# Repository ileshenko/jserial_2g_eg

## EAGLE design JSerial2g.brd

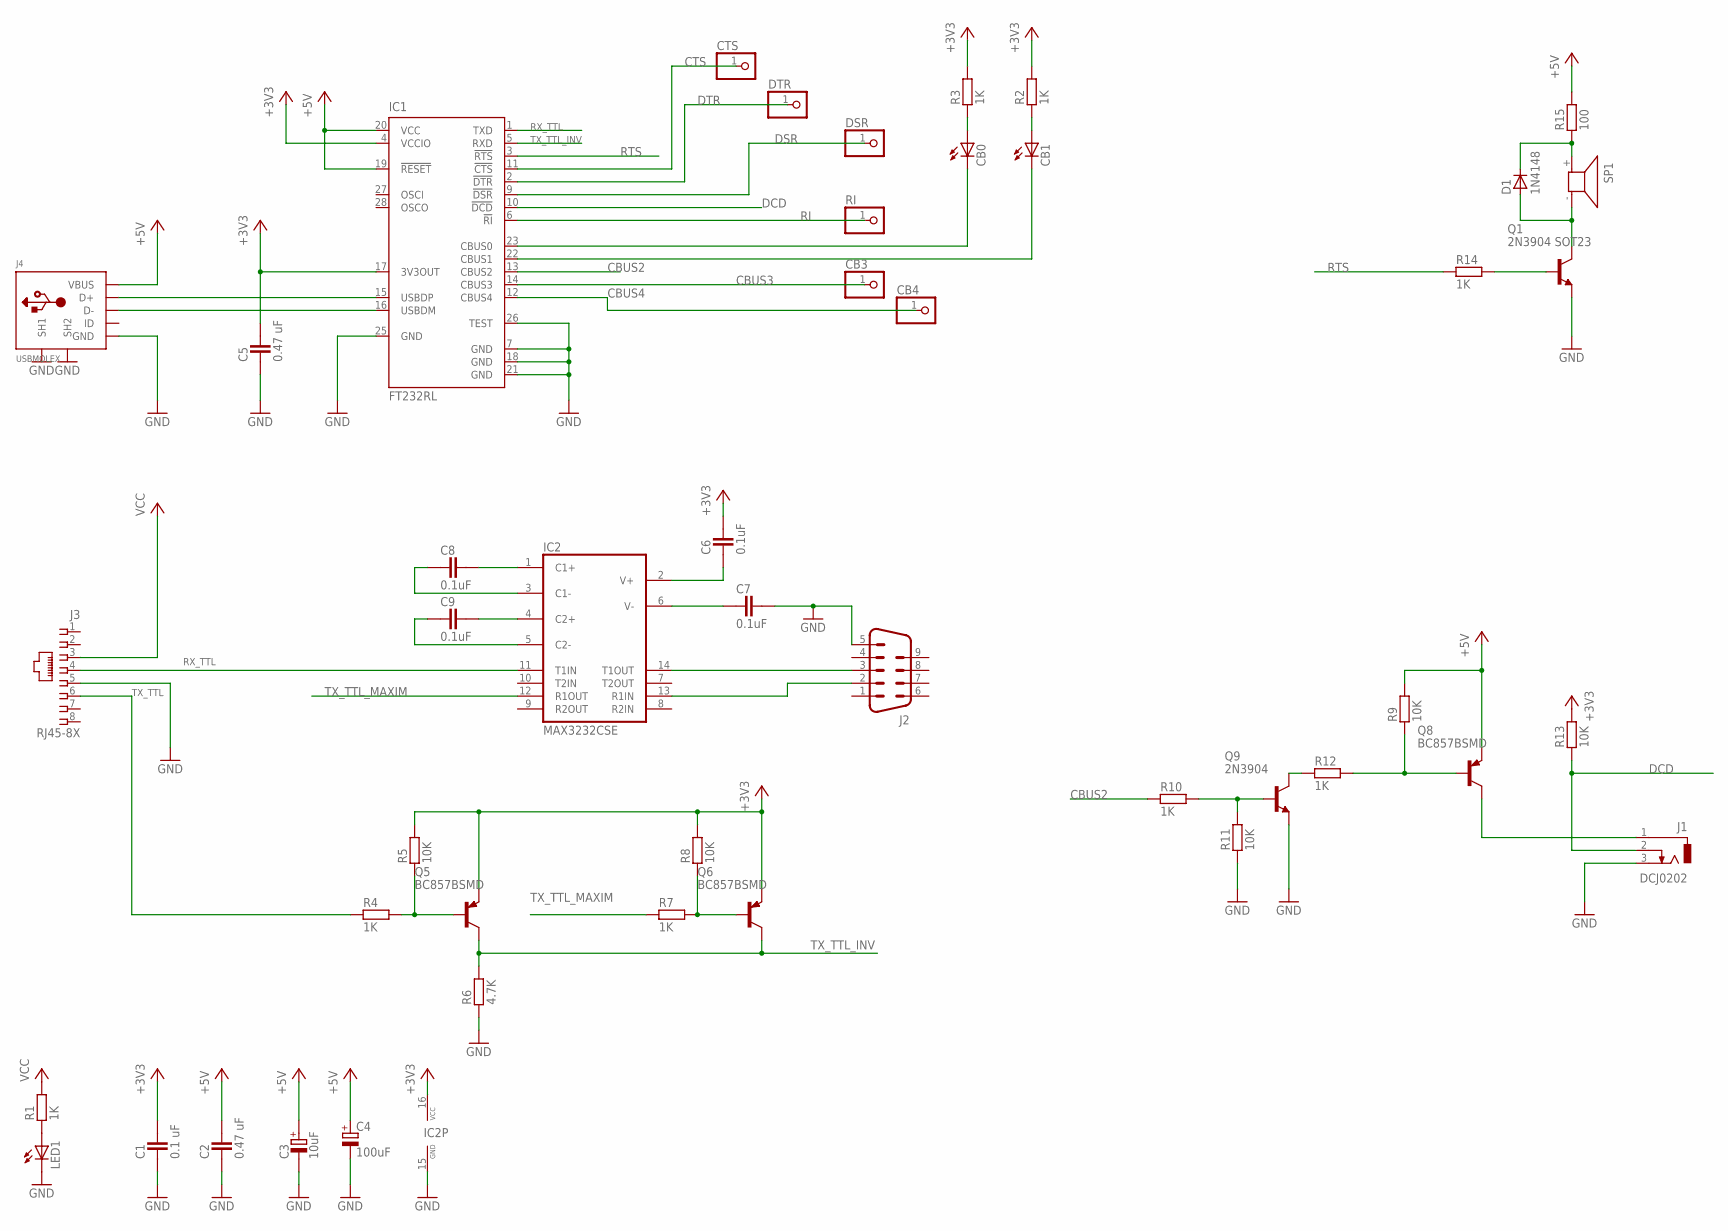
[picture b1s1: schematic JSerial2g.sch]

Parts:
C1: 0.1 uF; CAPC2012X145AN
C2, C5: 0.47 uF; CAPC2012X145AN
C3: 10uF; CAPMP3216X180N
C4: 100uF; E2,5-6
C6, C7, C8, C9: 0.1uF; CAPC2012X145AN
CB0, CB1: LED3MM
CB3, CB4: PINHD-1X1; 1X01
CTS: PINHD-1X1; 1X01
D1: 1N4148; SOD3718X135N
DSR: PINHD-1X1; 1X01
DTR: PINHD-1X1; 1X01
IC1: FT232RL; SSOP28
IC2: MAX3232CSE; SO16
J1: DCJ0202
J2: M09D
J3: RJ45-8X; RJ45-NO-SHIELD
J4: USBMOLEX; HW-MU-5F-20
LED1: LED3MM
Q1: 2N3904 SOT23; SOT95P280X135-3N
Q5, Q6, Q8: BC857BSMD; SOT23-BEC
Q9: 2N3904; SOT95P280X135-3N
R1, R2, R3, R4, R7, R10, R12, R14: 1K; RESC2012X70N
R5, R8, R9, R11, R13: 10K; RESC2012X70N
R6: 4.7K; RESC2012X70N
R15: 100; RESC2012X70N
RI: PINHD-1X1; 1X01
SP1: KSS1201

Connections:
+3V3: C1.2, C5.2, C6.2, IC1.4 (VCCIO), IC1.17 (3V3OUT), IC2.16 (VCC), Q5.E, Q6.E, R2.2, R3.2, R5.2, R8.2, R13.2
+5V: C2.2, C3.+, C4.+, IC1.19 (!RESET), IC1.20 (VCC), J4.VBUS, Q8.E, R9.2, R15.2
CBUS0: CB0.K (C), IC1.23 (CBUS0)
CBUS1: CB1.K (C), IC1.22 (CBUS1)
CBUS2: IC1.13 (CBUS2), R10.1
CBUS3: CB3.1, IC1.14 (CBUS3)
CBUS4: CB4.1, IC1.12 (CBUS4)
CTS: CTS.1, IC1.11 (!CTS)
DCD: IC1.10 (!DCD), J1.2, R13.1
DSR: DSR.1, IC1.9 (!DSR)
DTR: DTR.1, IC1.2 (!DTR)
GND: C1.1, C2.1, C3.-, C4.-, C5.1, C7.2, IC1.7 (GND), IC1.18 (GND), IC1.21 (GND), IC1.25 (GND), IC1.26 (TEST), IC2.15 (GND), J1.3, J2.5, J3.5, J4.GND, J4.SH1, J4.SH2, LED1.K (C), Q1.2 (E), Q9.2 (E), R6.1, R11.1
unnamed: LED1.A, R1.1
unnamed: C8.1, IC2.3 (C1-)
unnamed: IC1.15 (USBDP), J4.D+
unnamed: IC1.16 (USBDM), J4.D-
unnamed: CB1.A, R2.1
unnamed: CB0.A, R3.1
unnamed: C8.2, IC2.1 (C1+)
unnamed: C9.1, IC2.5 (C2-)
unnamed: C9.2, IC2.4 (C2+)
unnamed: C6.1, IC2.2 (V+)
unnamed: C7.1, IC2.6 (V-)
unnamed: IC2.14 (T1OUT), J2.3
unnamed: IC2.13 (R1IN), J2.2
unnamed: J1.1, Q8.C
unnamed: Q5.B, R4.2, R5.1
unnamed: Q6.B, R7.2, R8.1
unnamed: Q9.1 (B), R10.2, R11.2
unnamed: Q9.3 (C), R12.1
unnamed: Q8.B, R9.1, R12.2
unnamed: Q1.1 (B), R14.2
unnamed: D1.A, Q1.3 (C), SP1.- (2)
unnamed: D1.K, R15.1, SP1.+ (1)
RI: IC1.6 (!RI), RI.1
RTS: IC1.3 (!RTS), R14.1
RX_TTL: IC1.1 (TXD), IC2.11 (T1IN), J3.4
TX_TTL: J3.6, R4.1
TX_TTL_INV: IC1.5 (RXD), Q5.C, Q6.C, R6.2
TX_TTL_MAXIM: IC2.12 (R1OUT), R7.1
VCC: J3.3, R1.2

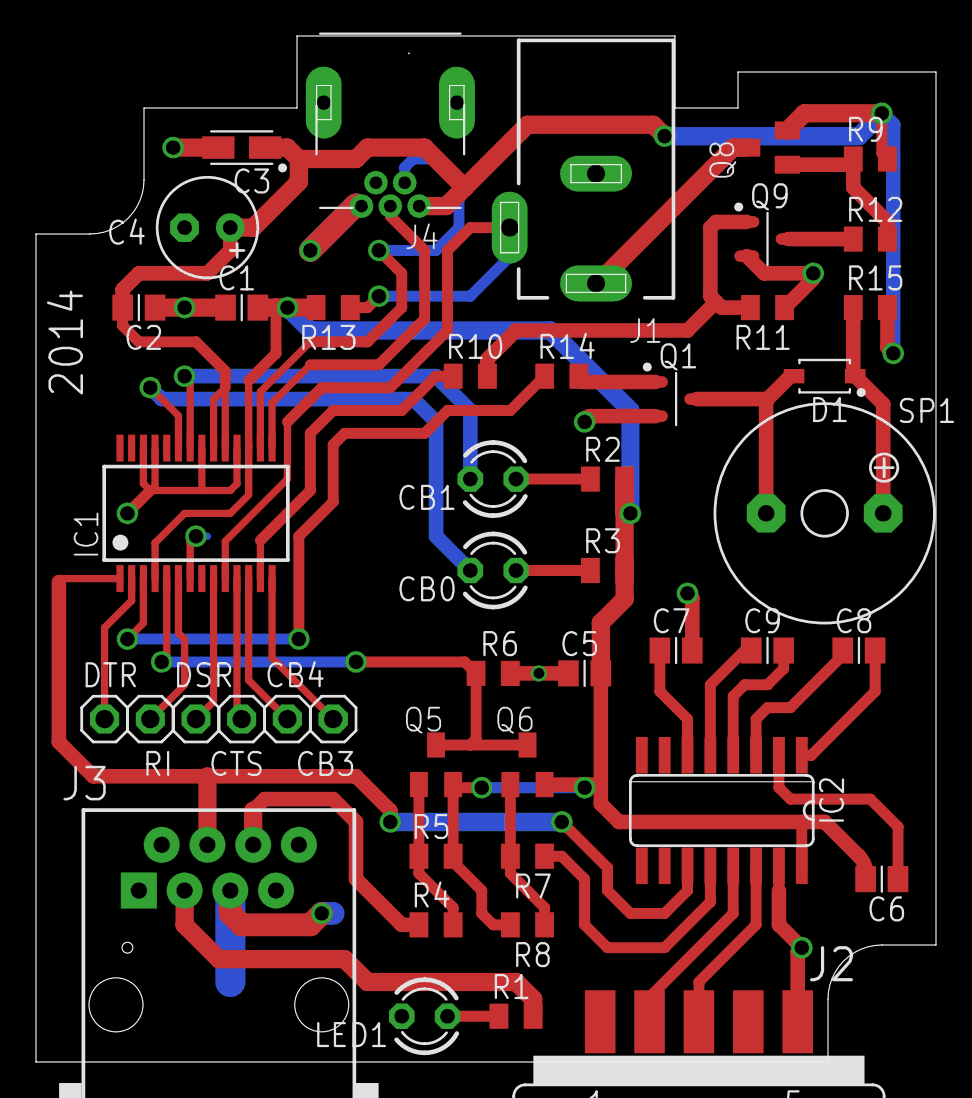
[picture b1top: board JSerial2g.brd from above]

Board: 2 copper layers, 50.0 x 57.0 mm, 46 parts (0 on the bottom side), 41 nets.

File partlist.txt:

Partlist

Exported from JSerial2g.sch at 7/23/14 4:36 PM

EAGLE Version 6.6.0 Copyright (c) 1988-2014 CadSoft

Assembly variant: 

Part     Value          Device           Package          Library             Sheet

C1       0.1 uF         CAPACITOR_0805   CAPC2012X145AN   ipc-7351-capacitor  1
C2       0.47 uF        CAPACITOR_0805   CAPC2012X145AN   ipc-7351-capacitor  1
C3       10uF           POLARISED_A_CASE CAPMP3216X180N   ipc-7351-capacitor  1
C4       100uF          CPOL-EUE2.5-6    E2,5-6           rcl                 1
C5       0.47 uF        CAPACITOR_0805   CAPC2012X145AN   ipc-7351-capacitor  1
C6       0.1uF          CAPACITOR_0805   CAPC2012X145AN   ipc-7351-capacitor  1
C7       0.1uF          CAPACITOR_0805   CAPC2012X145AN   ipc-7351-capacitor  1
C8       0.1uF          CAPACITOR_0805   CAPC2012X145AN   ipc-7351-capacitor  1
C9       0.1uF          CAPACITOR_0805   CAPC2012X145AN   ipc-7351-capacitor  1
CB0                     LED3MM           LED3MM           jlab                1
CB1                     LED3MM           LED3MM           jlab                1
CB3                     PINHD-1X1        1X01             pinhead             1
CB4                     PINHD-1X1        1X01             pinhead             1
CTS                     PINHD-1X1        1X01             pinhead             1
D1       1N4148         DIODE_SOD-123    SOD3718X135N     ipc-7351-diode      1
DSR                     PINHD-1X1        1X01             pinhead             1
DTR                     PINHD-1X1        1X01             pinhead             1
IC1      FT232RL        FT232RL          SSOP28           ftdichip            1
IC2      MAX3232CSE     MAX3232CSE       SO16             maxim               1
J1       DCJ0202        DCJ0202          DCJ0202          con-jack            1
J2                      M09D             M09D             jlab                1
J3       RJ45-8X        RJ45-8X          RJ45-NO-SHIELD   jlab                1
J4       USBMOLEX       USBMOLEX         HW-MU-5F-20      jlab_connectors     1
LED1                    LED3MM           LED3MM           jlab                1
Q1       2N3904 SOT23   NPN_SOT-23       SOT95P280X135-3N ipc-7351-transistor 1
Q5       BC857BSMD      BC857BSMD        SOT23-BEC        transistor-pnp      1
Q6       BC857BSMD      BC857BSMD        SOT23-BEC        transistor-pnp      1
Q8       BC857BSMD      BC857BSMD        SOT23-BEC        transistor-pnp      1
Q9       2N3904         NPN_SOT-23       SOT95P280X135-3N ipc-7351-transistor 1
R1       1K             RESISTOR_0805    RESC2012X70N     ipc-7351-resistor   1
R2       1K             RESISTOR_0805    RESC2012X70N     ipc-7351-resistor   1
R3       1K             RESISTOR_0805    RESC2012X70N     ipc-7351-resistor   1
R4       1K             RESISTOR_0805    RESC2012X70N     ipc-7351-resistor   1
R5       10K            RESISTOR_0805    RESC2012X70N     ipc-7351-resistor   1
R6       4.7K           RESISTOR_0805    RESC2012X70N     ipc-7351-resistor   1
R7       1K             RESISTOR_0805    RESC2012X70N     ipc-7351-resistor   1
R8       10K            RESISTOR_0805    RESC2012X70N     ipc-7351-resistor   1
R9       10K            RESISTOR_0805    RESC2012X70N     ipc-7351-resistor   1
R10      1K             RESISTOR_0805    RESC2012X70N     ipc-7351-resistor   1
R11      10K            RESISTOR_0805    RESC2012X70N     ipc-7351-resistor   1
R12      1K             RESISTOR_0805    RESC2012X70N     ipc-7351-resistor   1
R13      10K            RESISTOR_0805    RESC2012X70N     ipc-7351-resistor   1
R14      1K             RESISTOR_0805    RESC2012X70N     ipc-7351-resistor   1
R15      100            RESISTOR_0805    RESC2012X70N     ipc-7351-resistor   1
RI                      PINHD-1X1        1X01             pinhead             1
SP1                     KSS1201          KSS1201          buzzer              1

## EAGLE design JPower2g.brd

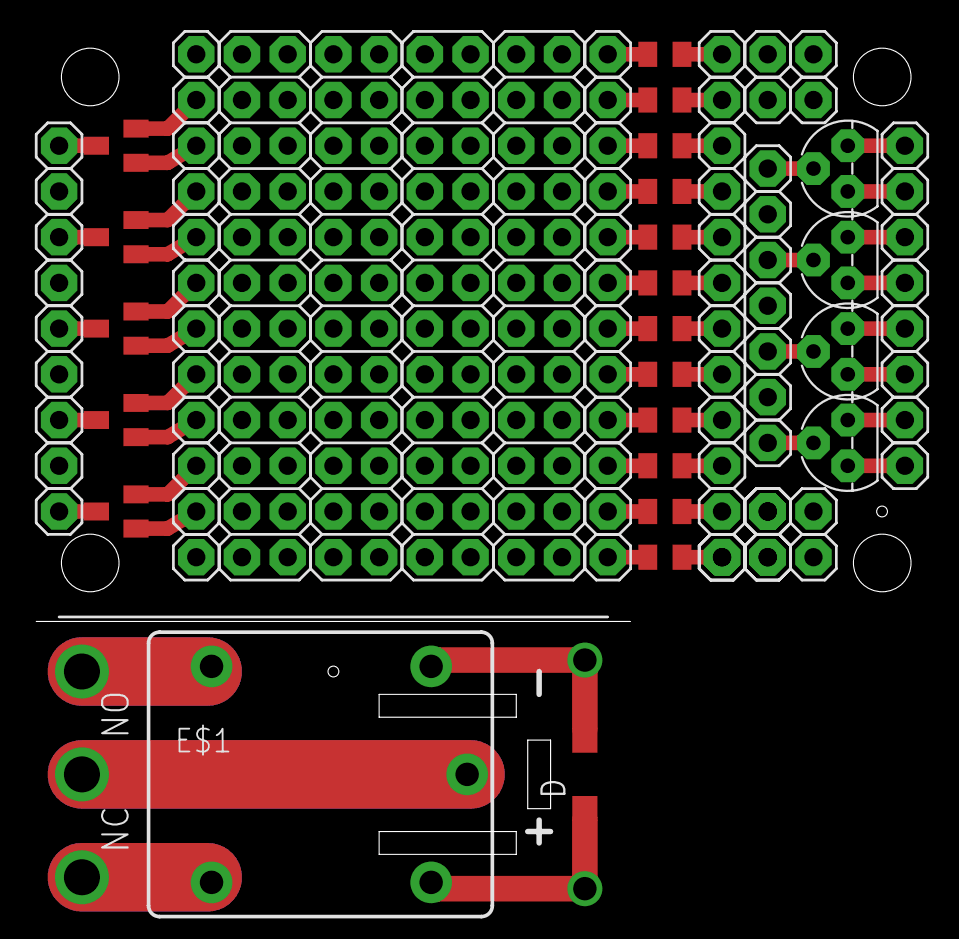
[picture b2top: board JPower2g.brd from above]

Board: 2 copper layers, 98 parts (0 on the bottom side), 51 nets.

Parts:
D: 1N4148; SOD123
E$1: SRD
E$2, E$3, E$4, E$5: 2X12
JP1, JP2, JP3, JP4, JP5, JP6, JP7, JP8, JP9, JP10, JP11, JP12, JP13, JP14, JP15, JP16, JP17, JP18, JP19, JP20, JP21, JP22, JP23, JP24, JP25, JP26, JP27, JP28, JP29, JP30, JP31, JP32, JP33, JP34, JP35, JP36, JP37, JP38, JP39, JP40, JP41, JP42, JP43, JP44, JP45, JP46, JP47, JP48, JP49, JP50, JP51, JP52, JP53, JP54, JP55, JP56, JP57, JP58, JP59, JP60, JP61, JP62, JP63, JP64, JP65, JP66, JP67, JP68, JP69, JP70, JP71: 1X01
Q1, Q3, Q4, Q5: BC547; TO92
Q2, Q6, Q7, Q8, Q9: 2N3904SOT23; SOT23-BEC
R1, R2, R3, R4, R5, R6, R7, R8, R9, R10, R11, R12: 270 R; RESC2012X70N

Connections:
unnamed: JP3.1, Q1.3
unnamed: JP4.1, Q1.1
unnamed: JP2.1, Q1.2
unnamed: JP6.1, Q3.3
unnamed: JP7.1, Q3.1
unnamed: JP5.1, Q3.2
unnamed: JP9.1, Q5.3
unnamed: JP11.1, Q5.1
unnamed: JP8.1, Q5.2
unnamed: JP15.1, Q6.C
unnamed: JP14.1, Q6.E
unnamed: JP13.1, Q6.B
unnamed: JP22.1, Q7.C
unnamed: JP21.1, Q7.E
unnamed: JP20.1, Q7.B
unnamed: JP27.1, Q8.C
unnamed: JP25.1, Q8.E
unnamed: JP24.1, Q8.B
unnamed: JP10.1, Q4.2
unnamed: JP12.1, Q2.B
unnamed: JP31.1, Q9.C
unnamed: JP30.1, Q9.E
unnamed: JP28.1, Q9.B
unnamed: JP32.1, R1.1
unnamed: JP18.1, Q4.3
unnamed: JP19.1, Q4.1
unnamed: JP33.1, R1.2
unnamed: JP23.1, R5.1
unnamed: JP34.1, R2.1
unnamed: JP35.1, R2.2
unnamed: JP36.1, R3.1
unnamed: JP17.1, Q2.C
unnamed: JP16.1, Q2.E
unnamed: JP37.1, R3.2
unnamed: JP26.1, R5.2
unnamed: JP38.1, R4.1
unnamed: JP39.1, R4.2
unnamed: JP40.1, R6.1
unnamed: JP41.1, R6.2
unnamed: JP42.1, R7.1
unnamed: JP43.1, R7.2
unnamed: JP44.1, R8.1
unnamed: JP45.1, R8.2
unnamed: JP46.1, R9.1
unnamed: JP47.1, R9.2
unnamed: JP48.1, R10.1
unnamed: JP49.1, R10.2
unnamed: JP50.1, R11.1
unnamed: JP51.1, R11.2
unnamed: JP52.1, R12.1
unnamed: JP53.1, R12.2

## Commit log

2014-03-02 first version - prototyping
2014-07-03 JSerial 2G in progress
2014-07-06 Work in progress
2014-07-07 layout tracing in progress
2014-07-08 layout finished. start review
2014-07-10 ver1.0 ready for production
2014-07-23 add stuff for assembling
2014-08-04 fix geometry after first production
